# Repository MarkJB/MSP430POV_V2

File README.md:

MSP430POV_V2
============

Revison 2 of the MSP430 based persistance of vision hardware.

The PCBs for this version are intended to be manufactured professionally.

================================HARDWARE=============================

22/07/2014 Received first batch of thru-hole PCBs. Assembled and tested board. When running on CR2302 works for about 30 seconds before locking up. Tried external 3V battery (2xAA) but exhibited same behaviour. Added 10uF cap. System locks up on CR2303 after about 30 seconds but runs fine on external 3V battery. Reflashed board (via P2 header connected to Launchpad) with current firmware and board set to 1MHz. Board now runs fine on CR2302. Need to determine if 10uF is necessary or if system is stable @ 1MHz without it.

To add a 1MHz board to Energia:

Add the follow to the boards.txt file in energia/hardware/msp430/boards.txt
```
##############################################################
lpmsp430g2553_1.name=LaunchPad w/ msp430g2553 (1MHz)
lpmsp430g2553_1.upload.protocol=rf2500
lpmsp430g2553_1.upload.maximum_size=16384
lpmsp430g2553_1.build.mcu=msp430g2553
lpmsp430g2553_1.build.f_cpu=1000000L
lpmsp430g2553_1.build.core=msp430
lpmsp430g2553_1.build.variant=launchpad
lpmsp430g2553_1.upload.maximum_ram_size=512
```
Restart Energia - check for extra board (Tools -> Boards)

28/07/2014 Received the first batch of SMT (surface mount) PCBs. Assembled and tested board without 10uF cap. Worked ok but two LEDs were out (P2.6 & P2.7). Checked LEDs and chip. Replaced chip. Same problem. Discovered that on blank chips the shared pins were in external xtal mode (P2.6 & P2.7 were set to xin and xout). Cleared the P2SEL register (setting all bits to zero) sets all pins to be port 2 input/outputs. 

Removed the 10uF cap from the thru-hole board and it works fine @ 1MHz. Don't think I need to alter the PCB to include it. Will need to see how well the boards perform as the battery voltage drops.

==========================FIRMWARE===================================

Master branch is the current stable v1.00 firmware.

It allows you to upload ASCII chars via serial. These messages are then stored in flash and will persist after power off.

If no message exists, the default pacman style ghost is displayed.

To upload ASCII messages, connect a serial terminal and power on and you will see info and a menu:
```
POV HW Rev 002 - firmware v1.00 - github.com/markjb/msp430pov_v2 - CCNC 2014
CPU Frequency = 1MHz
----------------------
Reading flash.........
Reading flash.....Done
----------------------
Commands (r)ead, (w)rite and (e)rase
```
Read  - will read the current content of the flash memory.
Erase - will erase the flash memory.
Write - will erase, write and read the flash memory.

You only need to use write as this will first call erase, then read, then write the message, then call read again.
```
w
----------------------
Erasing flash.........
Erasing flash.....Done
----------------------
Reading flash.........
Reading flash.....Done
----------------------
Commands (r)ead, (w)rite and (e)rase
----------------------
Write to flash........
Enter message to write to flash. Terminate string with a '.' (Message entry will timeout in 30 secs)
```
Type a message using the basic ASCII character set, end the message with a full stop (e.g. '.') and press return.
```
Hello World!.
Writing flash.........
Writing flash.....Done
----------------------
Reading flash.........
Reading flash.....Done
----------------------
Commands (r)ead, (w)rite and (e)rase
```
Extra debug output can be enabled by uncommenting the #define DEBUG lines in debug.h.

e.g. look for these lines and remove the //
```
//#define DEBUG1
//#define DEBUG2
//#define DEBUG_SLOWDOWN
```
DEBUG1 gives some extra info but should not interfere with normal operation.
DEBUG2 gives a lot more info and will slow down the led display. 
You will probably need to uncomment DEBUG_SLOWDOWN to add pauses between the debug statements.
Note: Debug adds about 2kb to the firmware size

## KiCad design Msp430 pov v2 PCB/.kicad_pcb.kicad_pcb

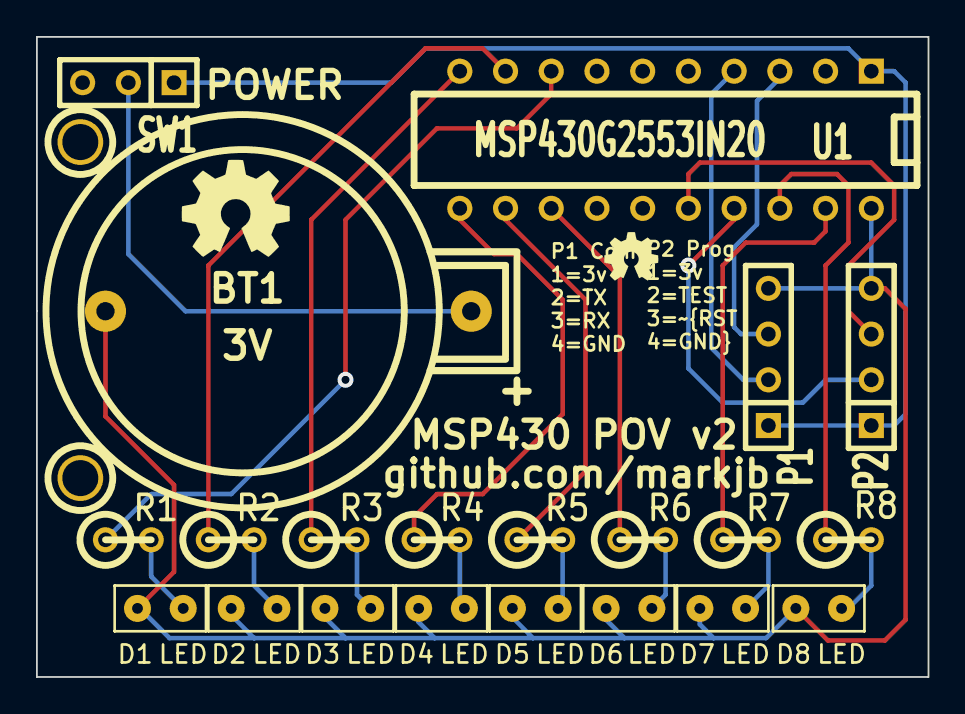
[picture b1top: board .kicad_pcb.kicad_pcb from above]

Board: 2 copper layers, 49.5 x 35.6 mm, 23 parts (0 on the bottom side), 23 nets.

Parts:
1PIN, 1PIN#2: P***; 2mm
BT1: 3V; CR2032H-Tayda
D1, D2, D3, D4, D5, D6, D7, D8: LED; LED_Rect
P1: SERIAL; SIL-4
P2: PROGRAM; SIL-4
R1, R2, R3, R4, R5, R6, R7, R8: R; R1
SW1: SPST; SIL-3
U1: MSP430G2553IN20; DIP-20__300

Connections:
unnamed: R2.1, U1.9
unnamed: R3.1, U1.10
unnamed: R4.1, U1.11
unnamed: R5.1, U1.12
unnamed: R6.1, U1.13
unnamed: R1.1, U1.8
unnamed: D8.2, R8.2
unnamed: D7.2, R7.2
unnamed: D6.2, R6.2
unnamed: P2.2, U1.17
unnamed: P2.3, U1.16
unnamed: P1.2, U1.4
unnamed: P1.3, U1.3
unnamed: D5.2, R5.2
unnamed: R8.1, U1.18
unnamed: R7.1, U1.19
unnamed: D1.2, R1.2
unnamed: BT1.1, SW1.2
unnamed: D2.2, R2.2
unnamed: D3.2, R3.2
unnamed: D4.2, R4.2
unnamed: P1.1, P2.1, SW1.1, U1.1
unnamed: BT1.2, D1.1, D2.1, D3.1, D4.1, D5.1, D6.1, D7.1, D8.1, P1.4, P2.4, U1.20

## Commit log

2014-07-06 Commit initial files
    Version 2 PCB kicad files and gerbers and basic firmware created in
    Energia
2014-07-22 Update after first hardware build
    Details of issues encountered and resolution
2014-07-28 Firmware update to set mode of shared pins
    On a blank chip the shared pins P2.6 & P2.7 were set to xin/xout. Needed
    to set all pins on port2 into output mode with P2SEL register.
2014-07-28 Updates for SMT boards
    Updates to firmware and readme. SMT PCBs have not changed
2014-07-28 Added pictures of boards
    Pictures of SMT and Thru-hole boards assembled and tested.
2014-07-28 Update README
    Added TODO: reminder to add infill on PCBs.
2014-07-31 Initial work on serial port message upload
    Add using serial port to upload message to display on the leds. Also
    added a command to reset display message (send 4 space chars in a row -
    but could be changed to something else). Mostly a proof of concept/debug
    tool for now.
2014-08-27 PDFs of PCBs and Schematic
    Added PDFs of Schematic and SMT & thru-hole PCBs as its a pain in the
    arse when you want to look at them on github and don't have the right
    software installed.
2014-09-14 extras
    Added a hybrid board for an kids soldering class. Includes a single
    redundant 1206 SMT cap as a first step in soldering SMT.
    Added the boards.txt file for Energia. This file includes the 1MHz G2553
    chip config.
    Cleaned up the basic test firmware.
2014-09-16 Write to/Read from flash working. Fonts lib included
    Code to erase/write/read flash working.
    Added fonts.h to convert ASCII to POV data.
    This was working for a little while on the smt rev2 board, but then it
    stopped working, can't input a message, serial comms routine isn't
    working. Have shifted the code around but no dice...
2014-09-16 Update msp430_pov_v2_firmware.ino
    Cleaned up basic test firmware. Added serial port output info.
2014-09-16 Flash read/write/erase & Serial message upload
    Flash read/write/erase working.
    Message upload using serial and ASCII chars (64 chars) working.
    Code needs tidying up need to look at a serial debug function (to turn
    all serial debug messages on/off easily rather than commenting them all
    out - code size dependant).
2014-09-17 #define debug added
    Added flag controllable debug statements using header macros. Can save a
    2k when all statements are disabled. Working as a proof of concept.
    Still need to work on what statements are at which level. Still need to
    tidy up code.
2014-09-18 Tidied up code, debug & comments
    This is v1.00.
2014-09-18 Updated readme
    Started to tidy up the readme and add instructions.
2014-09-18 Updated readme
    I accidentally used markdown.
    Hopefully this will fix it.
2014-09-18 Updated readme
    Didn't read the page on markdown correctly... 3rd times a charm.
    Otherwise I'm giving up for the evening!
2014-09-18 Minor change to comments
2014-10-29 Changed fonts.h
    Removed existing fonts.h and added one created from scratch. Font design
    files included.
    Also flipped default 'Pacman' style ghost to match new font.
2014-10-29 Update info in fonts.h
    Updated info on font editor in fonts.h
